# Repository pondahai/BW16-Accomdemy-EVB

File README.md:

# bw16
使用kicad設計
解開後，點兩下 .pro 即自動打開kicad

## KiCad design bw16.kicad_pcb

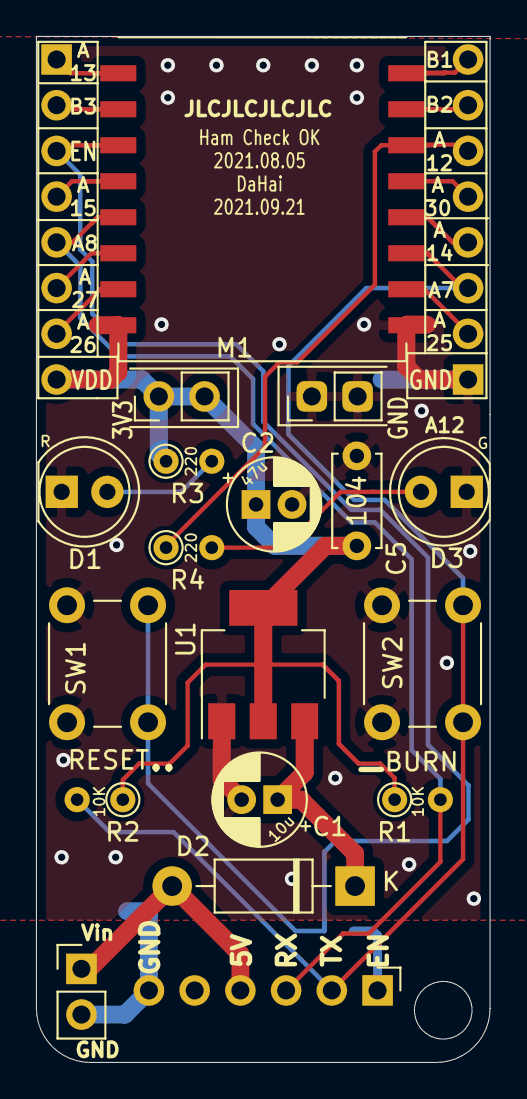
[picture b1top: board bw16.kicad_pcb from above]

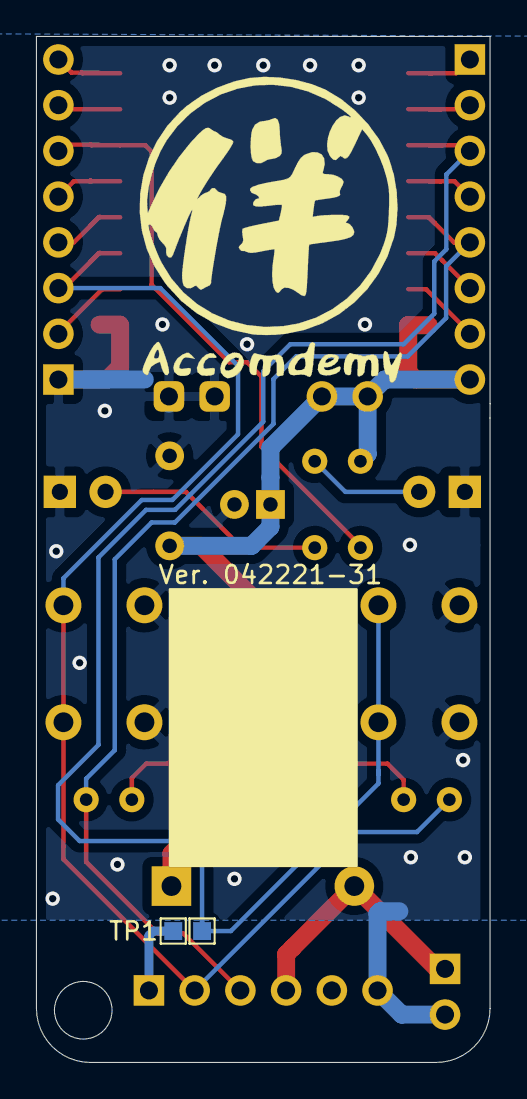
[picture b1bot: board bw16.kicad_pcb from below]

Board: 2 copper layers, 25.2 x 57.0 mm, 24 parts (3 on the bottom side), 21 nets.

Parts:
C1: 10u; CP_Radial_D5.0mm_P2.00mm
C2: 47u; CP_Radial_D5.0mm_P2.00mm
C5: 100n; C_Disc_D5.0mm_W2.5mm_P5.00mm
D1: RED; LED_D5.0mm_FlatTop
D2: 1N5819; D_DO-41_SOD81_P10.16mm_Horizontal
D3: GREEN; LED_D5.0mm_Clear
G1: LOGO; accomdemy
H4: MountingHole; MountingHole_3.2mm_M3
J1, J2: Conn_01x08_Male; PinHeader_1x08_P2.54mm_Vertical
J6: 3V3; PinHeader_1x02_P2.54mm_Vertical
J7: GND; PinHeader_1x02_P2.54mm_Vertical
J8: VIN; PinHeader_1x02_P2.54mm_Vertical
J9: Conn_01x06_Male; PinHeader_1x06_P2.54mm_Horizontal
M1: BW16
R1, R2: 10k; R_Axial_DIN0204_L3.6mm_D1.6mm_P2.54mm_Vertical
R3, R4: 220; R_Axial_DIN0204_L3.6mm_D1.6mm_P2.54mm_Vertical
SW1: RESET; SW_PUSH_6mm_H5mm
SW2: BURN; SW_PUSH_6mm_H5mm
TP1, TP2: TestPoint; TestPoint_Pad_1.0x1.0mm
U1: AP1117-33; SOT-223-3_TabPin2

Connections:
/EN: J1.3, M1.3, SW1.2, TP1.1
/GND: C1.2, C2.2, C5.2, D1.1, D3.1, J2.1, J7.1, J7.2, J8.2, J9.6, M1.9, SW1.1, SW2.1, U1.1
/LOG_RX: J1.5, J9.3, M1.5, R1.2
/LOG_TX: J2.3, J9.2, M1.11, R2.2, SW2.2
/PA12: J2.6, M1.14, R4.1
/VDD33: C2.1, C5.1, J1.8, J6.1, J6.2, M1.8, R1.1, R2.1, R3.1, U1.2
/VIN: D2.2, J8.1, J9.4
unnamed: C1.1, D2.1, U1.3
unnamed: D1.2, R3.2
unnamed: D3.2, R4.2
unnamed: J1.1, M1.1
unnamed: J1.2, M1.2
unnamed: J1.4, M1.4
unnamed: J1.6, M1.6
unnamed: J1.7, M1.7
unnamed: J2.2, M1.10
unnamed: J2.4, M1.12
unnamed: J2.5, M1.13
unnamed: J2.7, M1.15
unnamed: J2.8, M1.16
unnamed: J9.1, TP2.1

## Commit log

2021-08-02 BW16_3Dmodule
2021-08-04 accomdemy_bw16_keychain-3dModule
2021-08-04 wrl file for kicad_3Dmodule
2021-08-05 Add files via upload
    add some text to make soldering more easy
2021-08-05 add some text to make soldering more easy
2021-08-09 Add files via upload
    1.整理本地零件庫 bw16.kicad_mod
    2.加入qrcode測試。qrcode來源 http://qr.calm9.com/tw/ 尺寸:L 密度:1
2021-09-10 修改娟印層文字
    把接腳的arduino數字拿掉
    字大小與線條粗細改成JLC的建議值
